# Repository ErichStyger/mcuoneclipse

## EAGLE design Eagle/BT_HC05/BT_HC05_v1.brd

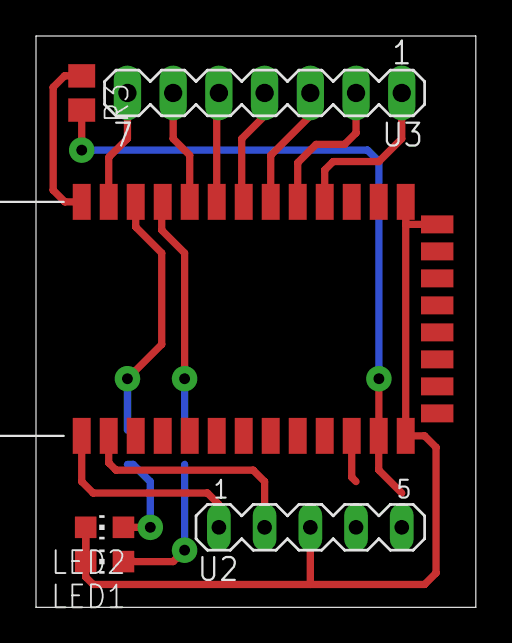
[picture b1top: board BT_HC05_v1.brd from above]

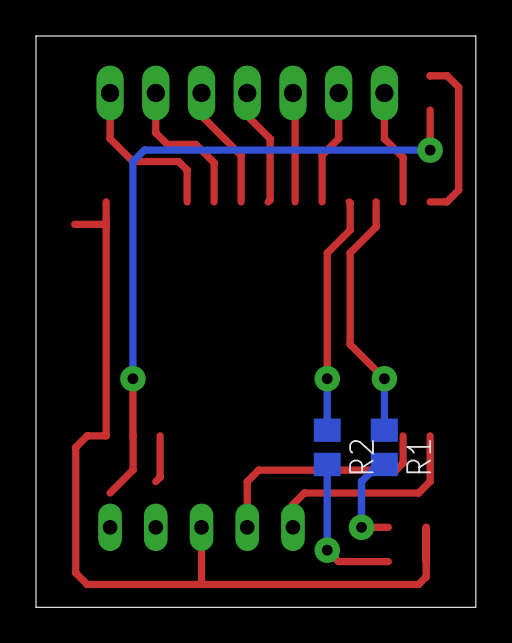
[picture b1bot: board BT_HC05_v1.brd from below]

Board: 2 copper layers, 24.4 x 31.7 mm, 8 parts (2 on the bottom side), 16 nets.

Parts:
LED1, LED2: SMD LED; CHIP-LED0805
R1, R2: 470; R0805
R3: 10K; R0805
U1: HC_05; BLUETOOTH_SMD
U2: Pin Row; MAR05-1
U3: Pin Row; MA07-1

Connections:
CMD: R3.1, U1.34
GND: LED1.C, LED2.C, U1.13, U1.21, U1.22, U2.3
LED1: R2.1, U1.31
LED2: R1.1, U1.32
unnamed: LED1.A, R2.2
unnamed: LED2.A, R1.2
PIO2: U1.25, U3.1
PIO3: U1.26, U3.2
PIO4: U1.27, U3.3
PIO5: U1.28, U3.4
PIO6: U1.29, U3.5
PIO7: U1.30, U3.6
PIO10: U1.33, U3.7
RX: U1.2, U2.2
TX: U1.1, U2.1
VCC: R3.2, U1.12
